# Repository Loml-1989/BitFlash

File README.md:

# BitFlash
A small USB C programmer for 25 series SPI flash and 24 series I2C EEPROMs  built around the WCH CH341A.

## Board Views

|                   Back                    |                   Front                   |
| :---------------------------------------: | :---------------------------------------: |
|  |  |

## Using the Target Socket (`J2`)

J2 is a standard 16 pin DIP socket split into two halves:
- Top half (Pins 1 to 4 / 13 to 16): 24xx I2C EEPROMs 
- Bottom half (Pins 5 to 12): 25xx SPI flash
## Schematic

## Software

BitFlash uses the fixed-function CH341A USB-to-SPI/I2C controller ASIC, so there is no onboard microcontroller . Host tools talk to it directly over USB.
## AI Disclosure
For this project AI was used for help me debug ERC and DRC issues.

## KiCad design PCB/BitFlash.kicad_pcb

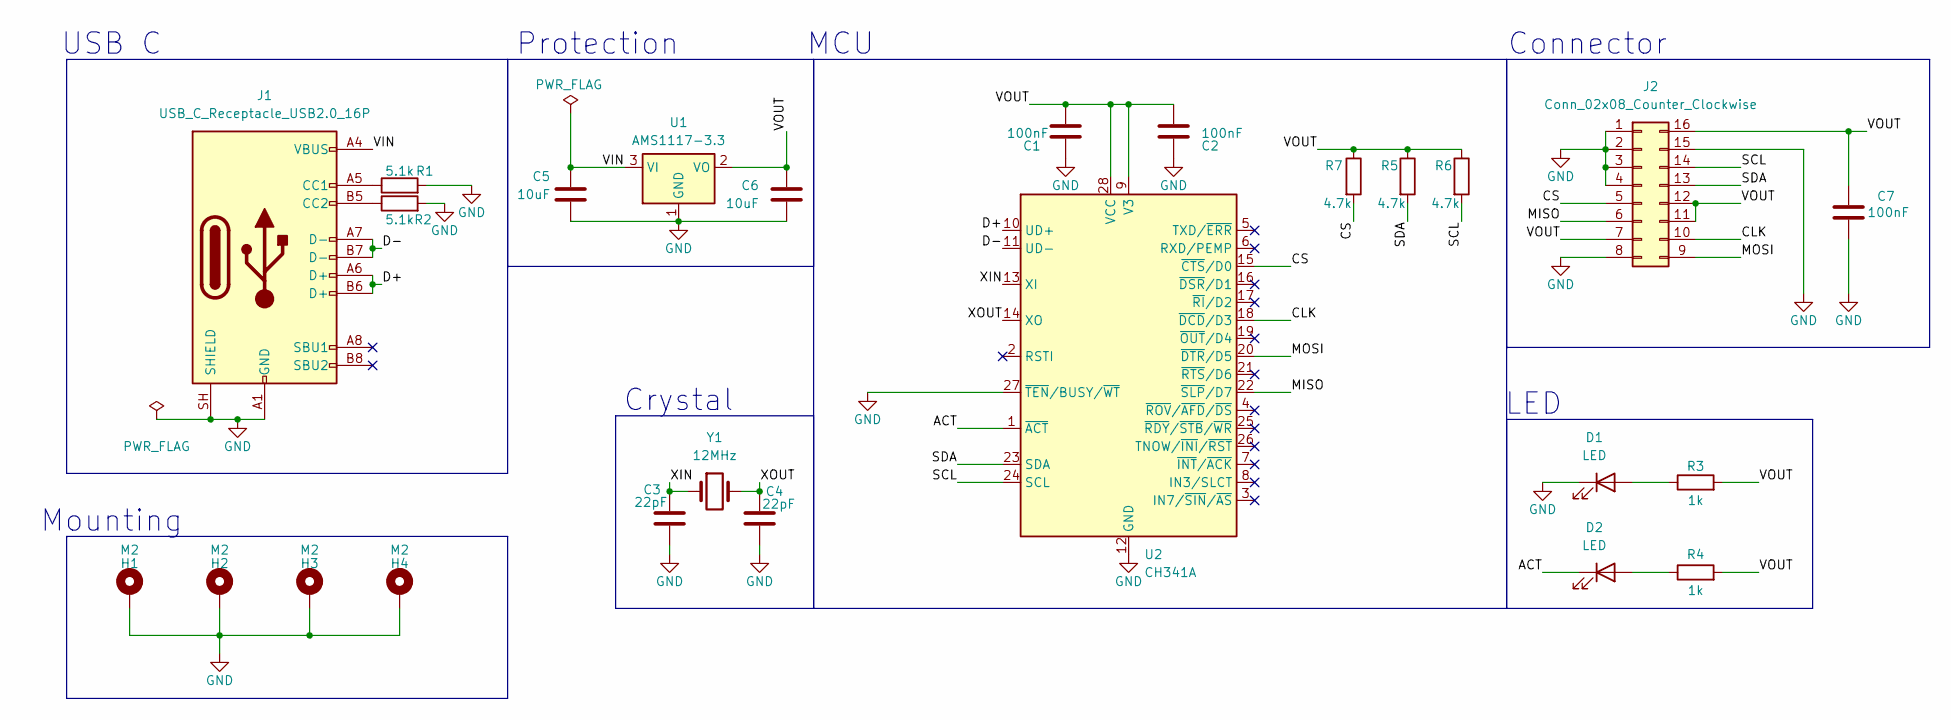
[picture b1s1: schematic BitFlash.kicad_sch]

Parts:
C1, C2, C7: 100nF; C_0603_1608Metric
C3, C4: 22pF; C_0603_1608Metric
C5, C6: 10uF; C_0603_1608Metric
D1, D2: LED; LED_D5.0mm
H1, H2, H3, H4: M2; MountingHole_2.2mm_M2_Pad
J1: USB_C_Receptacle_USB2.0_16P; USB_C_Receptacle_GCT_USB4105-xx-A_16P_TopMnt_Horizontal
J2: Conn_02x08_Counter_Clockwise; DIP-16_W7.62mm_Socket
R1, R2: 5.1k; R_0603_1608Metric
R3, R4: 1k; R_0603_1608Metric
R5, R6, R7: 4.7k; R_0603_1608Metric
U1: AMS1117-3.3; SOT-223-3_TabPin2
U2: CH341A; SOIC-28W_7.5x17.9mm_P1.27mm
Y1: 12MHz; Crystal_HC49-U_Vertical

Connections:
/ACT: D2.1 (K), U2.1 (~ACT)
/CLK: J2.10, U2.18 (~DCD/D3)
/CS: J2.5, R7.2, U2.15 (~CTS/D0)
/D+: J1.A6 (D+), J1.B6 (D+), U2.10 (UD+)
/D-: J1.A7 (D-), J1.B7 (D-), U2.11 (UD-)
/MISO: J2.6, U2.22 (~SLP/D7)
/MOSI: J2.9, U2.20 (~DTR/D5)
/SCL: J2.14, R6.2, U2.24 (SCL)
/SDA: J2.13, R5.2, U2.23 (SDA)
/VIN: C5.1, J1.A4 (VBUS), J1.A9 (VBUS), J1.B4 (VBUS), J1.B9 (VBUS), U1.3 (VI)
/VOUT: C1.1, C2.1, C6.1, C7.1, J2.7, J2.11, J2.12, J2.16, R3.2, R4.2, R5.1, R6.1, R7.1, U1.2 (VO), U2.9 (V3), U2.28 (VCC)
/XIN: C3.1, U2.13 (XI), Y1.1
/XOUT: C4.1, U2.14 (XO), Y1.2
GND: C1.2, C2.2, C3.2, C4.2, C5.2, C6.2, C7.2, D1.1 (K), H1.1 (1_1), H2.1 (1_1), H3.1 (1_1), H4.1 (1_1), J1.A1 (GND), J1.A12 (GND), J1.B1 (GND), J1.B12 (GND), J1.SH (SHIELD), J2.1, J2.2, J2.3, J2.4, J2.8, J2.15, R1.2, R2.2, U1.1 (GND), U2.12 (GND), U2.27 (~TEN/BUSY/~WT)
unnamed: D1.2 (A), R3.1
unnamed: D2.2 (A), R4.1
unnamed: J1.A5 (CC1), R1.1
unnamed: J1.B5 (CC2), R2.1

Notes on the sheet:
Connector
Protection
MCU
USB C
Crystal
LED
Mounting

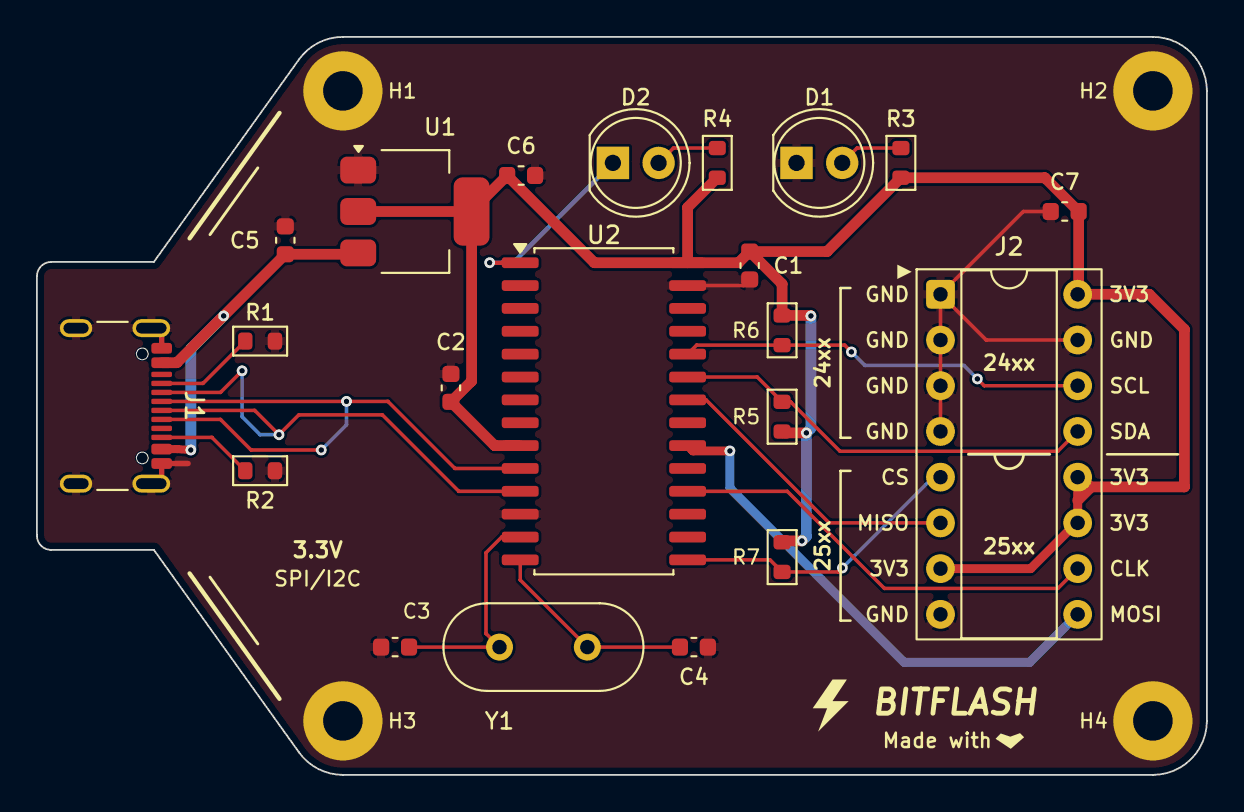
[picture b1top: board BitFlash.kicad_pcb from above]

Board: 2 copper layers, 65.0 x 41.0 mm, 25 parts (0 on the bottom side), 18 nets.

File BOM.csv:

Sr. No.,Designators,Component,Qty,Buy Link,Price (USD),Notes
1,U2,WCH CH341A USB-to-SPI/I2C Controller IC (SOIC-28W),1,https://robu.in/product/ch341a-24-25-series-eeprom-flash-bio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,2.55,"Harvest IC from CH341A donor module (~Rs.239 incl. GST; raw IC rarely stocked locally)"
2,U1,AMS1117-3.3 3.3V 1A LDO Voltage Regulator (SOT-223),1,https://robu.in/product/ams1117-3-3v-1a-sot-223-voltage-regu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,0.10,"~Rs.9/pc on Robu (pack of 5 option ~Rs.35-45)"
3,J1,USB Type-C 16-Pin SMD Receptacle (GCT USB4105-GF-A-060),1,https://in.element14.com/gct-global-connector-technology/usb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,1.05,"Rs.83.57 + GST (~Rs.99) on element14 India"
4,J2,16-Pin DIP IC Socket (7.62mm Pitch),1,https://robu.in/product/16-pin-dip-ic-socket-base-adaptor-pa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,0.10,"~Rs.8/pc (~Rs.30-35 per pack of 5)"
5,Y1,12 MHz Through-Hole Quartz Crystal (HC49-S / HC49-U),1,https://robu.in/product/hc49-s-12mhz-crystal-oscillator-pack-of-5/,0.10,"~Rs.10/pc (~Rs.40-50 per pack of 5; 4.88mm lead pitch fits HC49-U)"
6,"C1, C2, C7",100nF 50V 0603 X7R MLCC Capacitor,3,https://evelta.com/100nf-50v-10-x7r-0603-capacitor/,0.15,"Rs.4.60/pc incl. GST (Yageo CC0603KRX7R9BB104)"
7,"C3, C4",22pF 50V 0603 C0G/NP0 MLCC Capacitor,2,https://evelta.com/22pf-50v-5-c0g-0603-capacitor/,0.10,"Rs.3.54/pc incl. GST"
8,"C5, C6",10uF 50V 0603 MLCC Capacitor,2,https://robu.in/product/10uf-10000nf-50v-capacitor-0603-smd-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,0.10,"Rs.9.25 per pack of 5 (~Rs.1.85/pc)"
9,"R1, R2",5.1 kOhm 1% 0603 SMD Resistor (USB-C CC Pulldown),2,https://evelta.com/5-1-kohm-1-0603-thick-film-chip-resistor-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,0.05,"Rs.1.89/pc incl. GST (Yageo RC0603FR-075K1L)"
10,"R3, R4",1 kOhm 1% 0603 SMD Resistor (LED Current Limiter),2,https://evelta.com/1k-1-100mw-0603-chip-resistor/,0.05,"Rs.1.53/pc incl. GST (Yageo RC0603FR-071KL)"
11,"R5, R6, R7",4.7 kOhm 1% 0603 SMD Resistor (I2C/SPI Pull-ups),3,https://evelta.com/4-7k-1-0603-chip-resistor/,0.05,"Rs.1.53/pc incl. GST (Yageo RC0603FR-074K7L)"
12,D1,5mm Green Through-Hole LED (PWR),1,https://robu.in/product/5mm-green-dip-led-pack-of-50/,0.05,"~Rs.1.50/pc (~Rs.75 per pack of 50)"
13,D2,5mm Yellow Through-Hole LED (ACT),1,https://robu.in/product/5mm-dip-led-yellow-50-pcs/,0.05,"~Rs.0.81/pc (~Rs.41 per pack of 50)"
14,H1-H4,M2 x 8mm SS304 Button-Head Allen Screw (Optional),4,https://robu.in/product/m2-x-8mm-socket-button-head-cap-alle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,0.30,"Rs.74 per pack of 10 (~Rs.7.40/pc); optional PCB mounting hardware"
15,PCB,BitFlash 2-Layer Custom PCB (65 x 41 mm; 1.6mm; HASL),5,https://www.lioncircuits.com/quote,11.00,"LionCircuits PCB fabrication (flat $11 USD)"
16,-,Shipping (Estimated Domestic Component Shipping),1,,4.50,"Estimated domestic shipping (Robu + Evelta + element14; replace with exact checkout shipping for your pincode)"
,Total (including shipping),,,,20.30,"Components ($4.80) + 5x PCB ($11.00) + estimated component shipping ($4.50); verify pack minimums & HCB vendor acceptance before submitting"
